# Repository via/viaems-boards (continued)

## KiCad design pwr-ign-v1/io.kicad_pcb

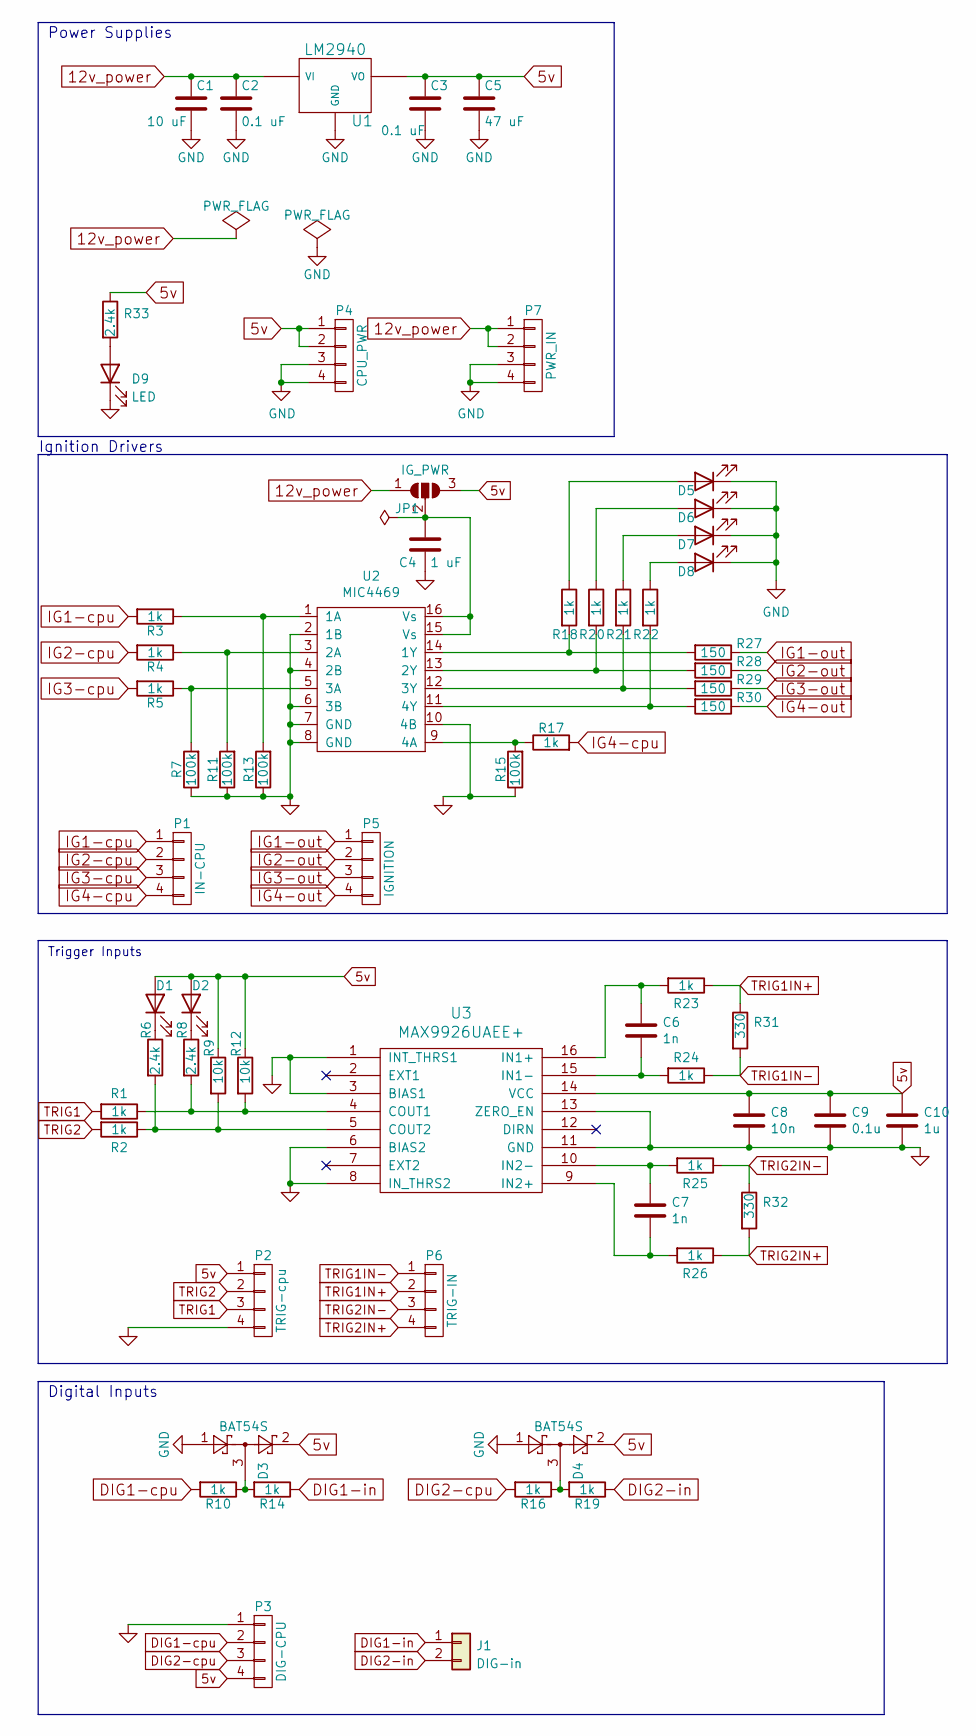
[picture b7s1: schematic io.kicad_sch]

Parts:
C1: 10 uF; C_0805_2012Metric_Pad1.18x1.45mm_HandSolder; Rating Tantalum 35V
C2, C3: 0.1 uF; C_0805_2012Metric_Pad1.18x1.45mm_HandSolder; Rating X7R
C4: 1 uF; C_0805_2012Metric_Pad1.18x1.45mm_HandSolder
C5: 47 uF; C_1206_3216Metric; Rating Tantalum 10V
C6, C7: 1n; C_0805_2012Metric_Pad1.18x1.45mm_HandSolder
C8: 10n; C_0805_2012Metric_Pad1.18x1.45mm_HandSolder
C9: 0.1u; C_0805_2012Metric_Pad1.18x1.45mm_HandSolder
C10: 1u; C_0805_2012Metric_Pad1.18x1.45mm_HandSolder
D1, D2, D5, D6, D7, D8, D9: LED; LED_0805_2012Metric_Pad1.15x1.40mm_HandSolder
D3, D4: BAT54S; SOT-23
J1: DIG-in; PinHeader_1x02_P2.54mm_Vertical
JP1: IG_PWR; SolderJumper-3_P1.3mm_Open_Pad1.0x1.5mm
P1: IN-CPU; PinHeader_1x04_P2.54mm_Vertical
P2: TRIG-cpu; PinHeader_1x04_P2.54mm_Vertical
P3: DIG-CPU; PinHeader_1x04_P2.54mm_Vertical
P4: CPU_PWR; PinHeader_1x04_P2.54mm_Vertical
P5: IGNITION; PinHeader_1x04_P2.54mm_Vertical
P6: TRIG-IN; PinHeader_1x04_P2.54mm_Vertical
P7: PWR_IN; PinHeader_1x04_P2.54mm_Vertical
R1, R2, R3, R4, R5, R10, R14, R16, R17, R18, R19, R20, R21, R22, R23, R24, R25, R26: 1k; R_0805_2012Metric_Pad1.20x1.40mm_HandSolder
R6, R8, R33: 2.4k; R_0805_2012Metric_Pad1.20x1.40mm_HandSolder
R7, R11, R13, R15: 100k; R_0805_2012Metric_Pad1.20x1.40mm_HandSolder
R9, R12: 10k; R_0805_2012Metric_Pad1.20x1.40mm_HandSolder
R27, R28, R29, R30: 150; R_0805_2012Metric_Pad1.20x1.40mm_HandSolder
R31, R32: 330; R_Axial_DIN0207_L6.3mm_D2.5mm_P2.54mm_Vertical
U1: LM2940; TO-220-3_Horizontal_TabDown
U2: MIC4469; SOIC-16W_7.5x10.3mm_P1.27mm
U3: MAX9926UAEE+; QSOP-16_3.9x4.9mm_P0.635mm

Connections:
5v: C3.1, C5.1, C8.1, C9.1, C10.1, D1.2 (A), D2.2 (A), D3.2, D4.2, JP1.3 (B), P2.1, P3.4, P4.1, P4.2, R9.1, R12.1, R33.1, U1.3 (VO), U3.14 (VCC)
12v_power: C1.1, C2.1, JP1.1 (A), P7.1, P7.2, U1.1 (VI)
DIG1-cpu: P3.2, R10.2
DIG1-in: J1.1, R14.1
DIG2-cpu: P3.3, R16.2
DIG2-in: J1.2, R19.1
GND: C1.2, C2.2, C3.2, C4.2, C5.2, C8.2, C9.2, C10.2, D3.1, D4.1, D5.1 (K), D6.1 (K), D7.1 (K), D8.1 (K), D9.1 (K), P2.4, P3.1, P4.3, P4.4, P7.3, P7.4, R7.1, R11.1, R13.1, R15.1, U1.2 (GND), U2.2 (1B), U2.4 (2B), U2.6 (3B), U2.7 (GND), U2.8 (GND), U2.10 (4B), U3.1 (INT_THRS1), U3.3 (BIAS1), U3.6 (BIAS2), U3.8 (IN_THRS2), U3.11 (GND), U3.13 (ZERO_EN)
IG1-cpu: P1.1, R3.2
IG1-out: P5.1, R27.1
IG2-cpu: P1.2, R4.2
IG2-out: P5.2, R28.1
IG3-cpu: P1.3, R5.2
IG3-out: P5.3, R29.1
IG4-cpu: P1.4, R17.2
IG4-out: P5.4, R30.1
unnamed: C4.1, JP1.2 (C), U2.15 (Vs), U2.16 (Vs)
unnamed: C6.1, R23.2, U3.16 (IN1+)
unnamed: C6.2, R24.2, U3.15 (IN1-)
unnamed: C7.1, R25.2, U3.10 (IN2-)
unnamed: C7.2, R26.2, U3.9 (IN2+)
unnamed: D1.1 (K), R6.1
unnamed: D2.1 (K), R8.1
unnamed: D3.3, R10.1, R14.2
unnamed: D4.3, R16.1, R19.2
unnamed: D5.2 (A), R18.1
unnamed: D6.2 (A), R20.1
unnamed: D7.2 (A), R21.1
unnamed: D8.2 (A), R22.1
unnamed: D9.2 (A), R33.2
unnamed: R1.1, R8.2, R12.2, U3.4 (COUT1)
unnamed: R2.1, R6.2, R9.2, U3.5 (COUT2)
unnamed: R5.1, R7.2, U2.5 (3A)
unnamed: R4.1, R11.2, U2.3 (2A)
unnamed: R3.1, R13.2, U2.1 (1A)
unnamed: R15.2, R17.1, U2.9 (4A)
unnamed: R18.2, R27.2, U2.14 (1Y)
unnamed: R20.2, R28.2, U2.13 (2Y)
unnamed: R21.2, R29.2, U2.12 (3Y)
unnamed: R22.2, R30.2, U2.11 (4Y)
TRIG1: P2.3, R1.2
TRIG1IN+: P6.2, R23.1, R31.1
TRIG1IN-: P6.1, R24.1, R31.2
TRIG2: P2.2, R2.2
TRIG2IN+: P6.4, R26.1, R32.2
TRIG2IN-: P6.3, R25.1, R32.1

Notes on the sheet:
Power Supplies
Ignition Drivers
Trigger Inputs
Digital Inputs

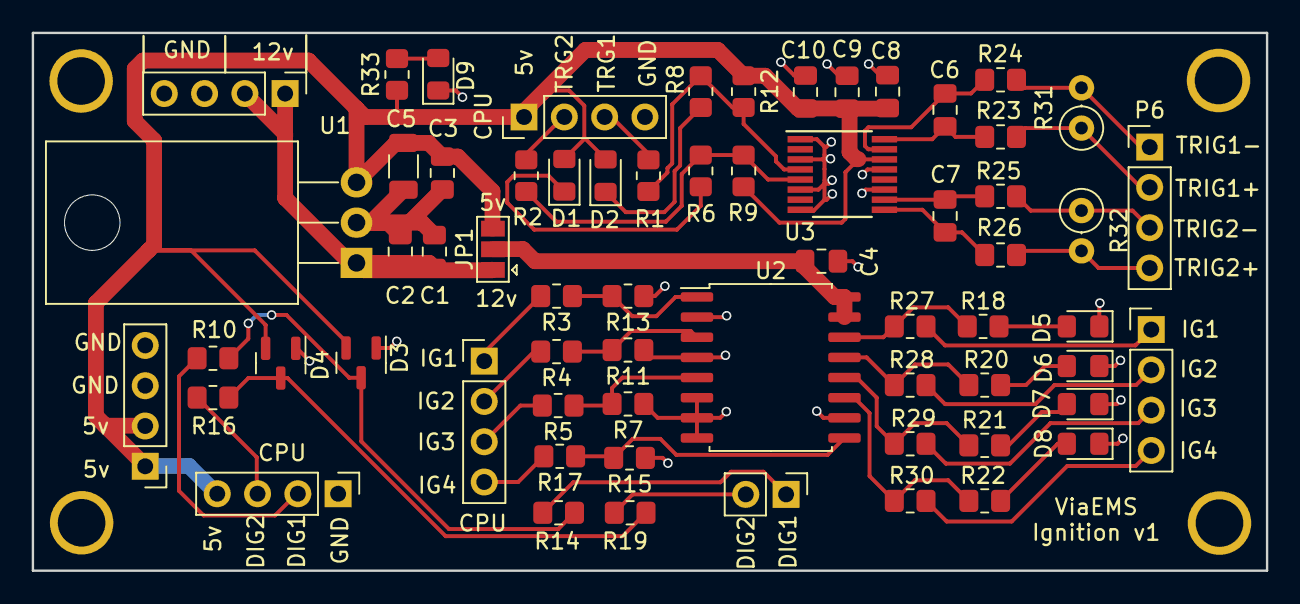
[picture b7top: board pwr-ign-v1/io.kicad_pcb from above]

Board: 2 copper layers, 77.8 x 33.9 mm, 64 parts (0 on the bottom side), 45 nets.

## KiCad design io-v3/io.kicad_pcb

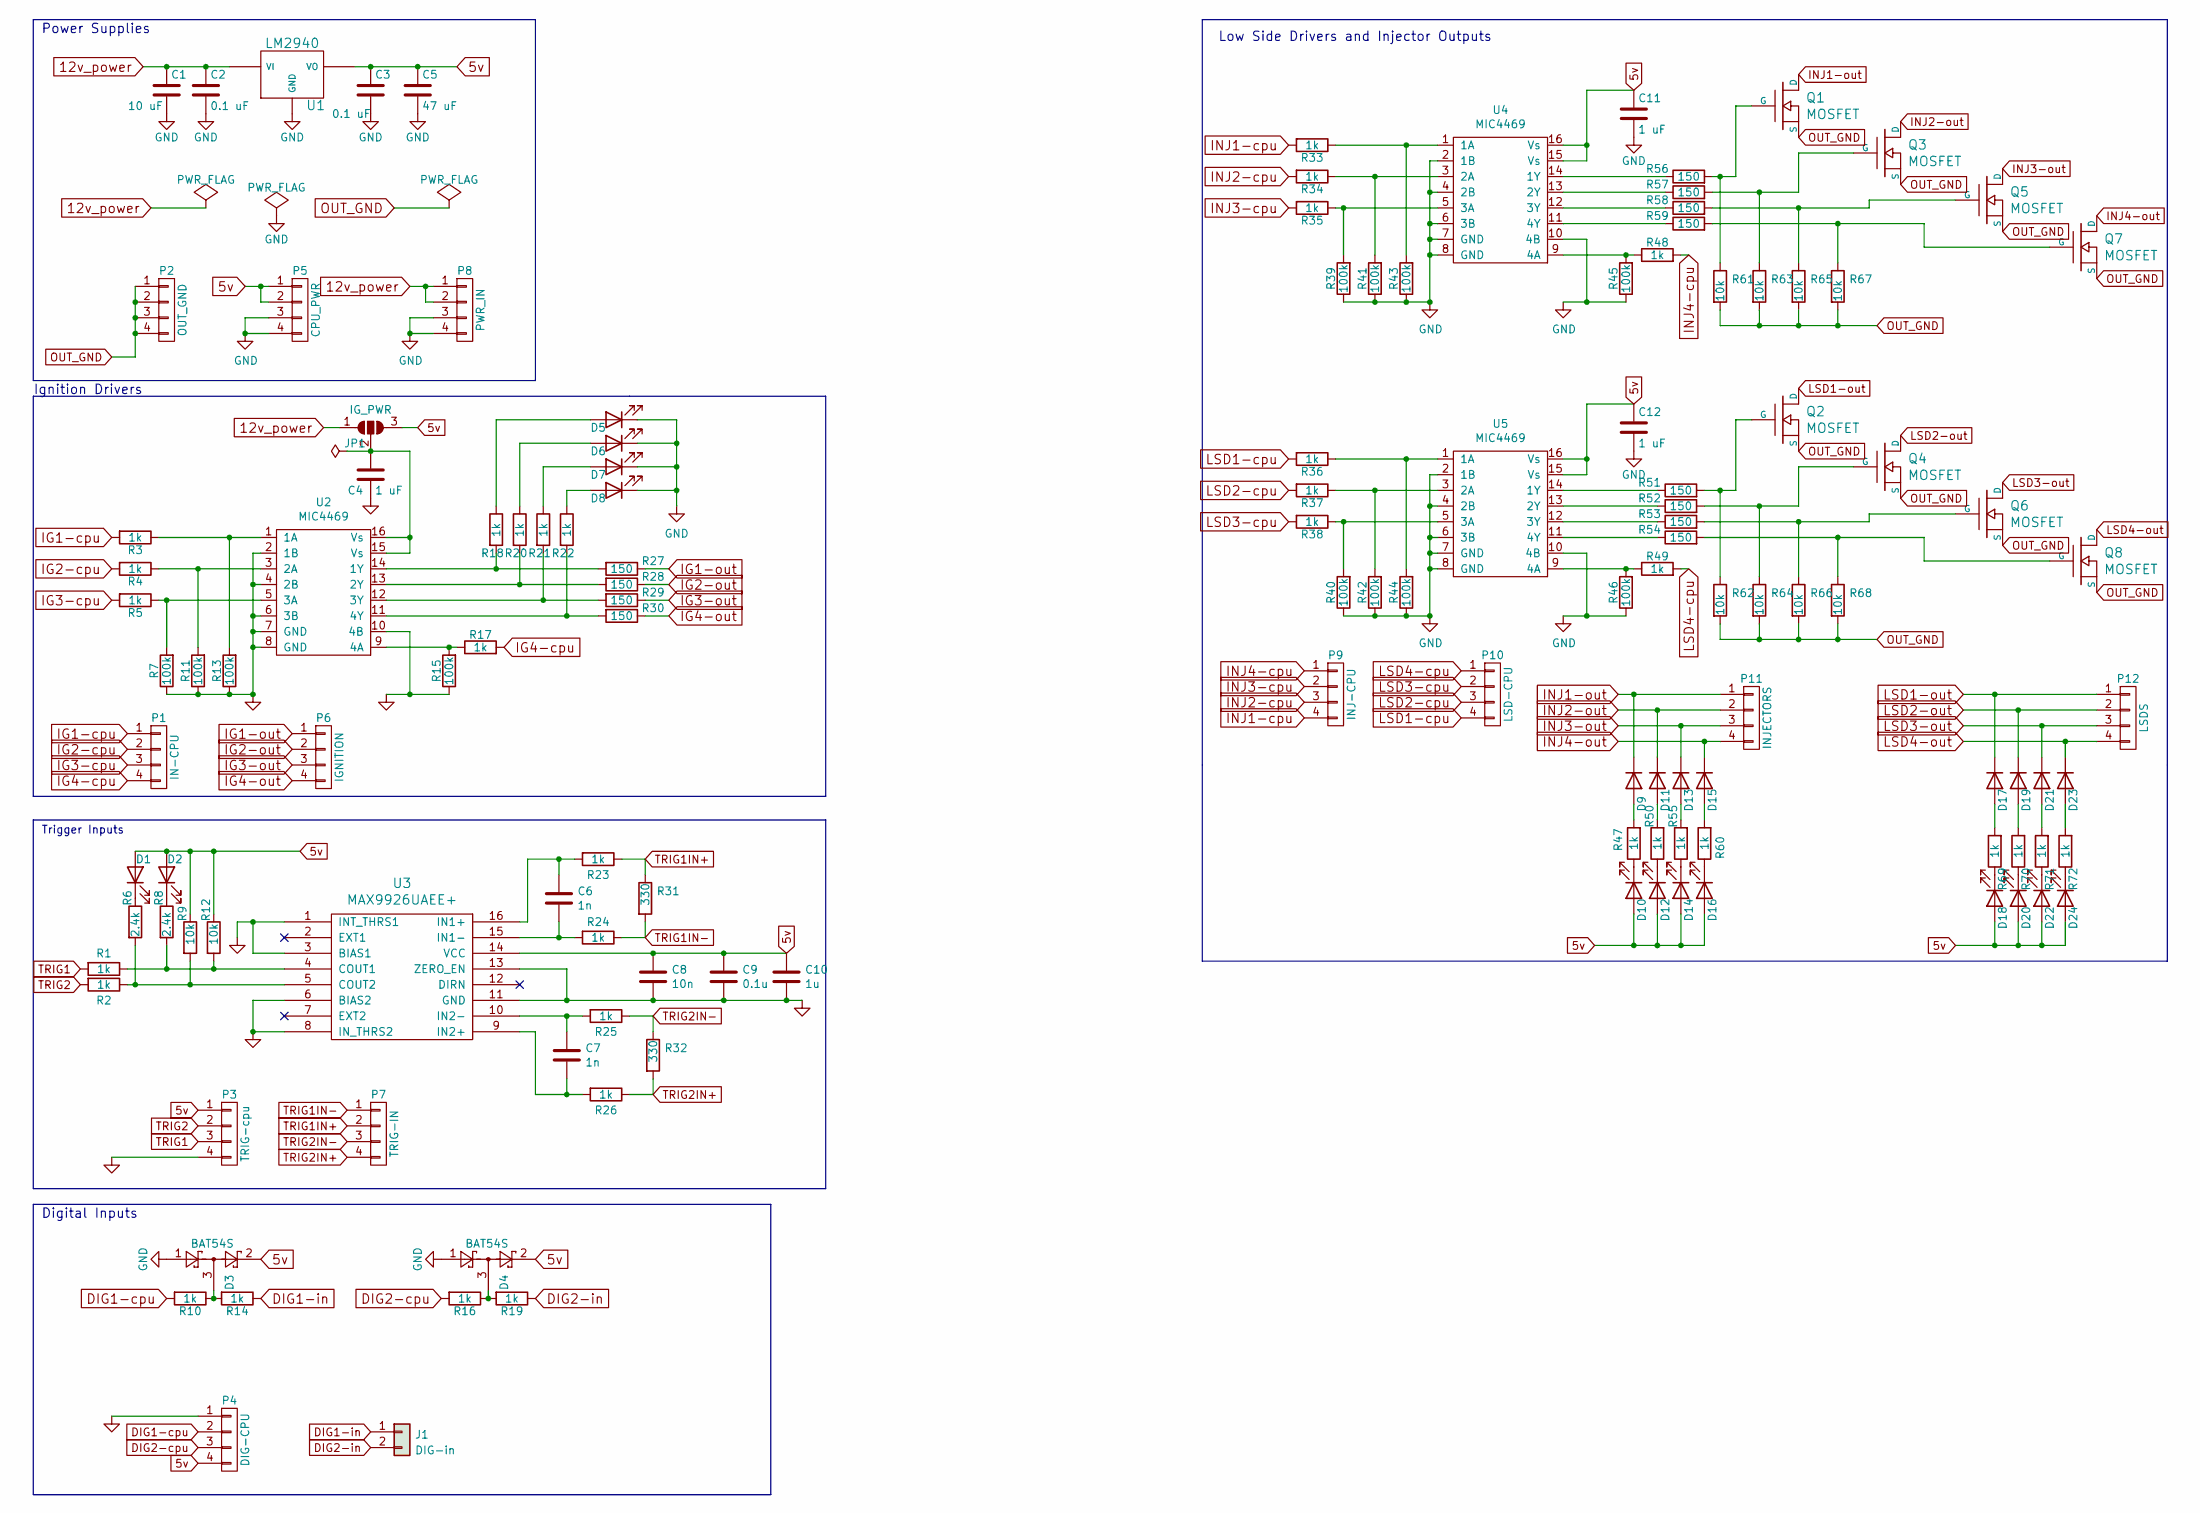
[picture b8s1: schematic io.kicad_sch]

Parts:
C1: 10 uF; C_0805_2012Metric_Pad1.18x1.45mm_HandSolder; Rating Tantalum 35V
C2, C3: 0.1 uF; C_0805_2012Metric_Pad1.18x1.45mm_HandSolder; Rating X7R
C4, C11, C12: 1 uF; C_0805_2012Metric_Pad1.18x1.45mm_HandSolder
C5: 47 uF; C_1206_3216Metric; Rating Tantalum 10V
C6, C7: 1n; C_0805_2012Metric_Pad1.18x1.45mm_HandSolder
C8: 10n; C_0805_2012Metric_Pad1.18x1.45mm_HandSolder
C9: 0.1u; C_0805_2012Metric_Pad1.18x1.45mm_HandSolder
C10: 1u; C_0805_2012Metric_Pad1.18x1.45mm_HandSolder
D1, D2, D5, D6, D7, D8, D10, D12, D14, D16, D18, D20, D22, D24: LED; LED_0805_2012Metric_Pad1.15x1.40mm_HandSolder
D3, D4: BAT54S; SOT-23
D9, D11, D13, D15, D17, D19, D21, D23: 1N4148; D_0805_2012Metric_Pad1.15x1.40mm_HandSolder
J1: DIG-in; PinHeader_1x02_P2.54mm_Vertical
JP1: IG_PWR; SolderJumper-3_P1.3mm_Open_Pad1.0x1.5mm
P1: IN-CPU; PinHeader_1x04_P2.54mm_Vertical
P2: OUT_GND; PinHeader_1x04_P2.54mm_Vertical
P3: TRIG-cpu; PinHeader_1x04_P2.54mm_Vertical
P4: DIG-CPU; PinHeader_1x04_P2.54mm_Vertical
P5: CPU_PWR; PinHeader_1x04_P2.54mm_Vertical
P6: IGNITION; PinHeader_1x04_P2.54mm_Vertical
P7: TRIG-IN; PinHeader_1x04_P2.54mm_Vertical
P8: PWR_IN; PinHeader_1x04_P2.54mm_Vertical
P9: INJ-CPU; PinHeader_1x04_P2.54mm_Vertical
P10: LSD-CPU; PinHeader_1x04_P2.54mm_Vertical
P11: INJECTORS; PinHeader_1x04_P2.54mm_Vertical
P12: LSDS; PinHeader_1x04_P2.54mm_Vertical
Q1, Q2, Q3, Q4, Q5, Q6, Q7, Q8: MOSFET; TO-252-2
R1, R2, R3, R4, R5, R10, R14, R16, R17, R18, R19, R20, R21, R22, R23, R24, R25, R26, R33, R34, R35, R36, R37, R38, R47, R48, R49, R50, R55, R60, R69, R70, R71, R72: 1k; R_0805_2012Metric_Pad1.20x1.40mm_HandSolder
R6, R8: 2.4k; R_0805_2012Metric_Pad1.20x1.40mm_HandSolder
R7, R11, R13, R15, R39, R40, R41, R42, R43, R44, R45, R46: 100k; R_0805_2012Metric_Pad1.20x1.40mm_HandSolder
R9, R12, R61, R62, R63, R64, R65, R66, R67, R68: 10k; R_0805_2012Metric_Pad1.20x1.40mm_HandSolder
R27, R28, R29, R30, R51, R52, R53, R54, R56, R57, R58, R59: 150; R_0805_2012Metric_Pad1.20x1.40mm_HandSolder
R31, R32: 330; R_Axial_DIN0207_L6.3mm_D2.5mm_P2.54mm_Vertical
U1: LM2940; TO-220-3_Horizontal_TabDown
U2, U4, U5: MIC4469; SOIC-16W_7.5x10.3mm_P1.27mm
U3: MAX9926UAEE+; QSOP-16_3.9x4.9mm_P0.635mm

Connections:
5v: C3.1, C5.1, C8.1, C9.1, C10.1, C11.1, C12.1, D1.2 (A), D2.2 (A), D3.2, D4.2, D10.2 (A), D12.2 (A), D14.2 (A), D16.2 (A), D18.2 (A), D20.2 (A), D22.2 (A), D24.2 (A), JP1.3 (B), P3.1, P4.4, P5.1, P5.2, R9.1, R12.1, U1.3 (VO), U3.14 (VCC), U4.15 (Vs), U4.16 (Vs), U5.15 (Vs), U5.16 (Vs)
12v_power: C1.1, C2.1, JP1.1 (A), P8.1, P8.2, U1.1 (VI)
DIG1-cpu: P4.2, R10.2
DIG1-in: J1.1, R14.1
DIG2-cpu: P4.3, R16.2
DIG2-in: J1.2, R19.1
GND: C1.2, C2.2, C3.2, C4.2, C5.2, C8.2, C9.2, C10.2, C11.2, C12.2, D3.1, D4.1, D5.1 (K), D6.1 (K), D7.1 (K), D8.1 (K), P3.4, P4.1, P5.3, P5.4, P8.3, P8.4, R7.1, R11.1, R13.1, R15.1, R39.1, R40.1, R41.1, R42.1, R43.1, R44.1, R45.1, R46.1, U1.2 (GND), U2.2 (1B), U2.4 (2B), U2.6 (3B), U2.7 (GND), U2.8 (GND), U2.10 (4B), U3.1 (INT_THRS1), U3.3 (BIAS1), U3.6 (BIAS2), U3.8 (IN_THRS2), U3.11 (GND), U3.13 (ZERO_EN), U4.2 (1B), U4.4 (2B), U4.6 (3B), U4.7 (GND), U4.8 (GND), U4.10 (4B), U5.2 (1B), U5.4 (2B), U5.6 (3B), U5.7 (GND), U5.8 (GND), U5.10 (4B)
IG1-cpu: P1.1, R3.2
IG1-out: P6.1, R27.1
IG2-cpu: P1.2, R4.2
IG2-out: P6.2, R28.1
IG3-cpu: P1.3, R5.2
IG3-out: P6.3, R29.1
IG4-cpu: P1.4, R17.2
IG4-out: P6.4, R30.1
INJ1-cpu: P9.4, R33.2
INJ1-out: D9.1 (K), P11.1, Q1.2 (D)
INJ2-cpu: P9.3, R34.2
INJ2-out: D11.1 (K), P11.2, Q3.2 (D)
INJ3-cpu: P9.2, R35.2
INJ3-out: D13.1 (K), P11.3, Q5.2 (D)
INJ4-cpu: P9.1, R48.2
INJ4-out: D15.1 (K), P11.4, Q7.2 (D)
LSD1-cpu: P10.4, R36.2
LSD1-out: D17.1 (K), P12.1, Q2.2 (D)
LSD2-cpu: P10.3, R37.2
LSD2-out: D19.1 (K), P12.2, Q4.2 (D)
LSD3-cpu: P10.2, R38.2
LSD3-out: D21.1 (K), P12.3, Q6.2 (D)
LSD4-cpu: P10.1, R49.2
LSD4-out: D23.1 (K), P12.4, Q8.2 (D)
unnamed: C4.1, JP1.2 (C), U2.15 (Vs), U2.16 (Vs)
unnamed: C6.1, R23.2, U3.16 (IN1+)
unnamed: C6.2, R24.2, U3.15 (IN1-)
unnamed: C7.1, R25.2, U3.10 (IN2-)
unnamed: C7.2, R26.2, U3.9 (IN2+)
unnamed: D1.1 (K), R6.1
unnamed: D2.1 (K), R8.1
unnamed: D3.3, R10.1, R14.2
unnamed: D4.3, R16.1, R19.2
unnamed: D5.2 (A), R18.1
unnamed: D6.2 (A), R20.1
unnamed: D7.2 (A), R21.1
unnamed: D8.2 (A), R22.1
unnamed: D9.2 (A), R47.2
unnamed: D11.2 (A), R50.2
unnamed: D13.2 (A), R55.2
unnamed: D15.2 (A), R60.2
unnamed: Q1.1 (G), R56.2, R61.1
unnamed: Q2.1 (G), R51.2, R62.1
unnamed: Q3.1 (G), R57.2, R63.1
unnamed: Q4.1 (G), R52.2, R64.1
unnamed: Q5.1 (G), R58.2, R65.1
unnamed: Q6.1 (G), R53.2, R66.1
unnamed: Q7.1 (G), R59.2, R67.1
unnamed: Q8.1 (G), R54.2, R68.1
unnamed: R1.1, R8.2, R12.2, U3.4 (COUT1)
unnamed: R2.1, R6.2, R9.2, U3.5 (COUT2)
unnamed: R5.1, R7.2, U2.5 (3A)
unnamed: R4.1, R11.2, U2.3 (2A)
unnamed: R3.1, R13.2, U2.1 (1A)
unnamed: R15.2, R17.1, U2.9 (4A)
unnamed: R18.2, R27.2, U2.14 (1Y)
unnamed: R20.2, R28.2, U2.13 (2Y)
unnamed: R21.2, R29.2, U2.12 (3Y)
unnamed: R22.2, R30.2, U2.11 (4Y)
unnamed: R33.1, R43.2, U4.1 (1A)
unnamed: R34.1, R41.2, U4.3 (2A)
unnamed: R35.1, R39.2, U4.5 (3A)
unnamed: R36.1, R44.2, U5.1 (1A)
unnamed: R37.1, R42.2, U5.3 (2A)
unnamed: R38.1, R40.2, U5.5 (3A)
unnamed: R45.2, R48.1, U4.9 (4A)
unnamed: R46.2, R49.1, U5.9 (4A)
unnamed: D10.1 (K), R47.1
unnamed: D12.1 (K), R50.1
unnamed: R51.1, U5.14 (1Y)
unnamed: R52.1, U5.13 (2Y)
unnamed: R53.1, U5.12 (3Y)
unnamed: R54.1, U5.11 (4Y)
unnamed: D14.1 (K), R55.1
unnamed: R56.1, U4.14 (1Y)
unnamed: R57.1, U4.13 (2Y)
unnamed: R58.1, U4.12 (3Y)
unnamed: R59.1, U4.11 (4Y)
unnamed: D16.1 (K), R60.1
unnamed: D18.1 (K), R69.1
unnamed: D17.2 (A), R69.2
unnamed: D20.1 (K), R70.1
unnamed: D19.2 (A), R70.2
unnamed: D22.1 (K), R71.1
unnamed: D21.2 (A), R71.2
unnamed: D24.1 (K), R72.1
unnamed: D23.2 (A), R72.2
OUT_GND: P2.1, P2.2, P2.3, P2.4, Q1.3 (S), Q2.3 (S), Q3.3 (S), Q4.3 (S), Q5.3 (S), Q6.3 (S), Q7.3 (S), Q8.3 (S), R61.2, R62.2, R63.2, R64.2, R65.2, R66.2, R67.2, R68.2
TRIG1: P3.3, R1.2
TRIG1IN+: P7.2, R23.1, R31.1
TRIG1IN-: P7.1, R24.1, R31.2
TRIG2: P3.2, R2.2
TRIG2IN+: P7.4, R26.1, R32.2
TRIG2IN-: P7.3, R25.1, R32.1

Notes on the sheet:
Power Supplies
Ignition Drivers
Trigger Inputs
Digital Inputs
Low Side Drivers and Injector Outputs

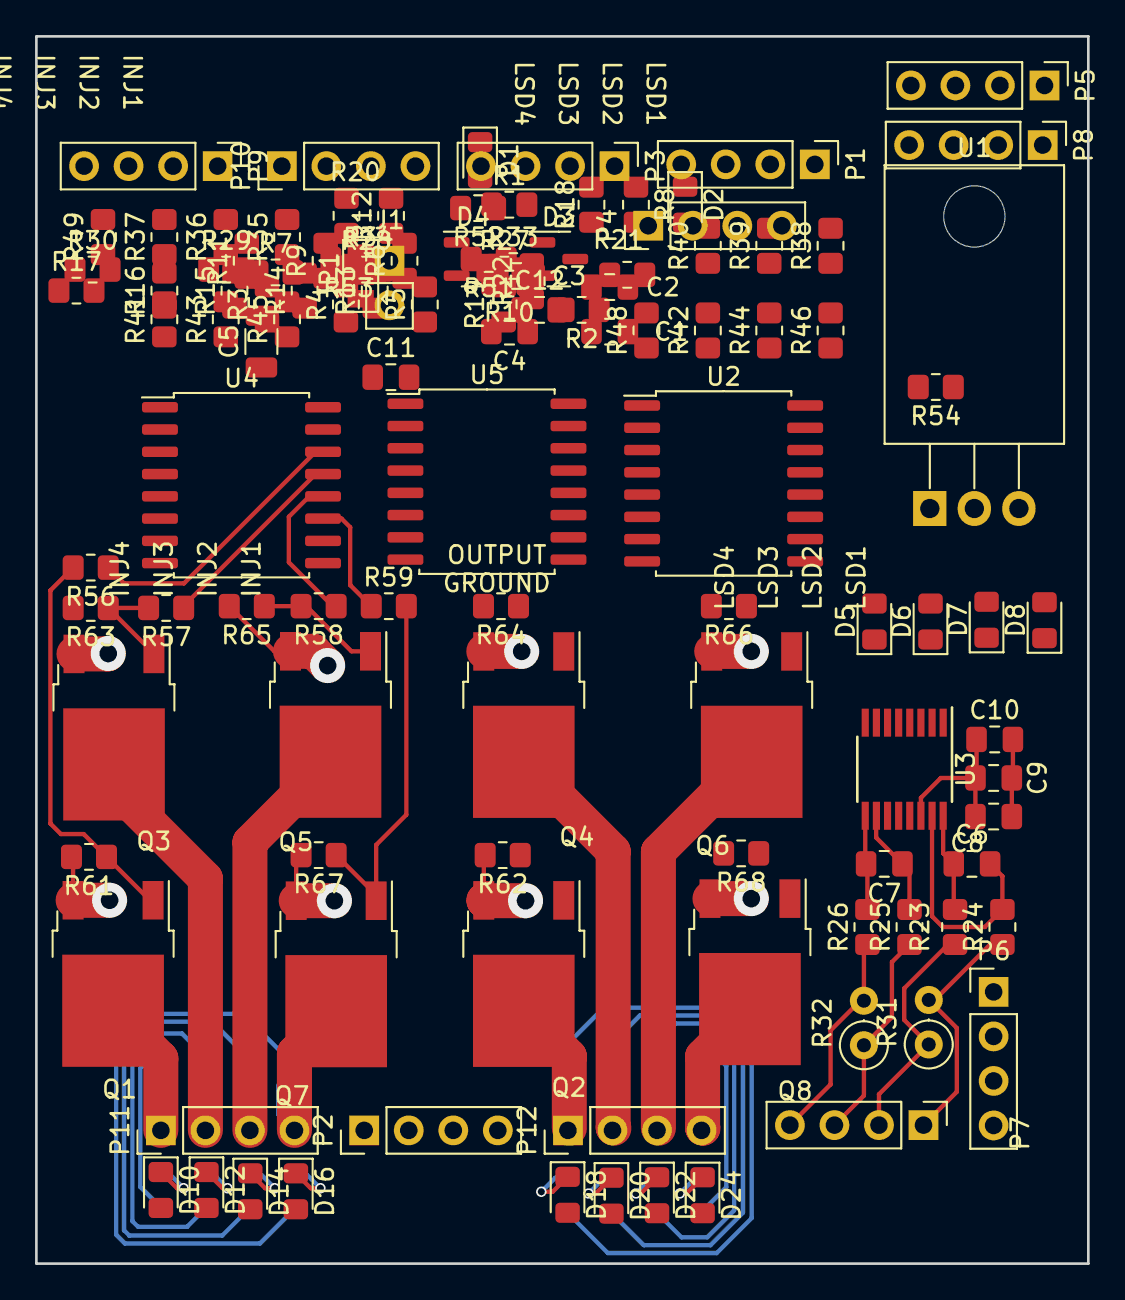
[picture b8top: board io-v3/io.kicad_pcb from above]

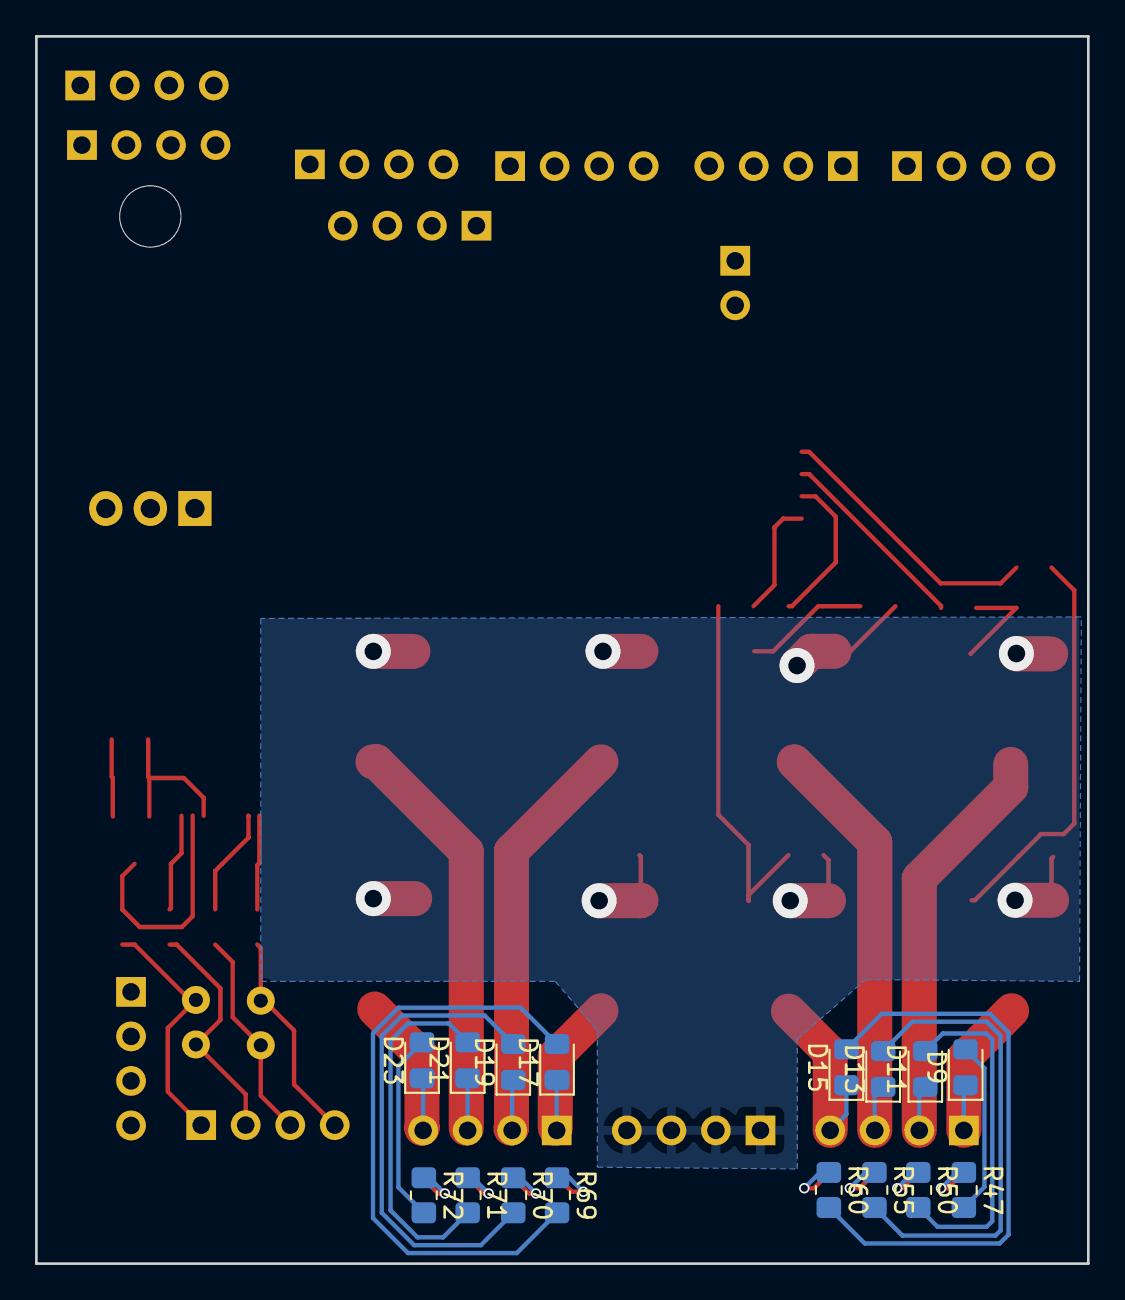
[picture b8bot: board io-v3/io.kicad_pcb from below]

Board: 2 copper layers, 60.0 x 70.0 mm, 135 parts (16 on the bottom side), 101 nets.

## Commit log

2019-12-29 Inital work on viaems-mini
2020-04-17 More updates
2020-09-30 Progress
2020-10-10 more
2020-12-18 Add prototyping board based on stm32f427
2020-12-18 move analog to opposite end
2022-12-25 Add various other experimental boards.
    IO V1 and Analog V1 are the original testing boards, all throughhole. The
    analog board uses a tlc2543 and still would work, but the IO board needs
    proper gate drivers to have acceptable FET speeds. Analog V2 uses a max11632
    which may or may not be a failed experiment. IO v2 adds trigger input
    handling, and uses mic4469's to drive FETs, and is usable except its a bit
    too big for my needs.
2022-12-25 experiments with a different form factor for the io board
2022-12-25 analog-v3, now with a tlc2553, two knock sensor inputs, all the cores, and 3 spares
2022-12-26 Add LEDs and make a board size
2022-12-27 Rework IO board to just be an LSD breakout board
2022-12-27 rename io-v3 to lsd-v1
2022-12-28 generate
2022-12-29 Add "Ignition V1" board for power supply, 4x ignition outputs, 2x VR inputs, and 2 digital inputs
2022-12-31 WIP updates for proto board to make smaller
2022-12-31 Add new IO board without LSD's, just 4x ignition, 2x VR, 2x digital input, and a 5v supply
2022-12-31 Add old Viaems board
2022-12-31 Add some readme stuff
2023-05-11 New stm32f4 board
2023-05-16 add some pin-1 markers
2023-05-16 Readme updates
2023-05-16 bleh
2023-05-16 New improved core board for stm32f427
2023-05-16 Change out footprint for stm32h7 and rewire pins to accomodate
    Same basic board, but now should mostly support the F7 and H7 series
2024-10-03 initial work on some s32k34x board
2024-10-17 more work on s32k3
2025-07-07 add .gitignore
2025-07-07 test-harness: initial pass
2025-07-10 bump
2025-10-24 move test harness work to dedicated branch
2025-10-30 Add gerbers for original board
2025-10-30 Test harness v2
2025-10-30 finalize
2026-05-07 Implement
2026-05-07 fixup! Implement
2026-05-08 Implement an MCXE24x LQFP64 core board.
2026-05-10 MCXC244 Prototyping board
    Intended for USB/UART comms
